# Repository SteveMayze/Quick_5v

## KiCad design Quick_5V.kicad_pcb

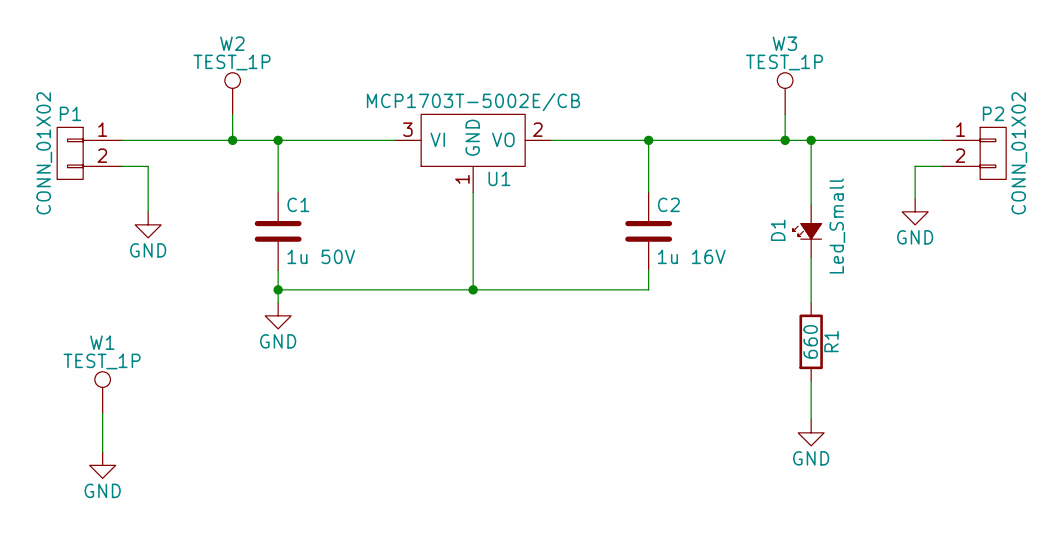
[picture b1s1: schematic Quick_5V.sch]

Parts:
C1: 1u 50V; C_0805_HandSoldering
C2: 1u 16V; C_0805_HandSoldering; Digikey-PN Value
D1: Led_Small; LED_0805
P1, P2: CONN_01X02; Pin_Header_Straight_1x02_Pitch2.54mm
R1: 660; R_0805_HandSoldering
U1: MCP1703T-5002E/CB; SOT-23A
W1: TEST_1P; Pin_Header_Straight_1x01_Pitch2.54mm
W2, W3: TEST_1P; Measurement_Point_Round-SMD-Pad_Small

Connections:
GND: C1.2, C2.2, P1.2, P2.2, R1.2, U1.1 (GND), W1.1
unnamed: C1.1, P1.1, U1.3 (VI), W2.1
unnamed: C2.1, D1.2 (A), P2.1, U1.2 (VO), W3.1
unnamed: D1.1 (K), R1.1

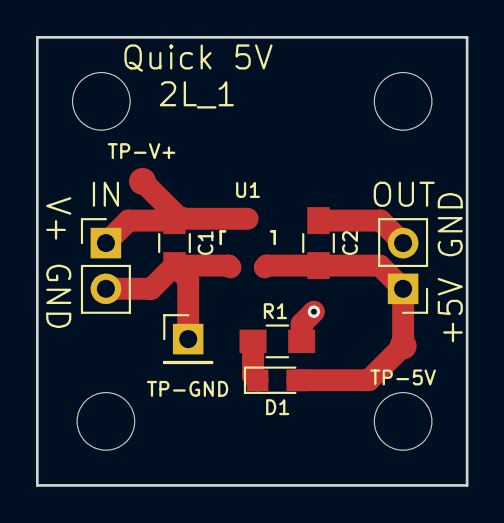
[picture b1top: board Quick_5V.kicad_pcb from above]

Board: 2 copper layers, 23.9 x 24.9 mm, 10 parts (0 on the bottom side), 4 nets.

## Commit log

2017-03-30 Initial checkin
